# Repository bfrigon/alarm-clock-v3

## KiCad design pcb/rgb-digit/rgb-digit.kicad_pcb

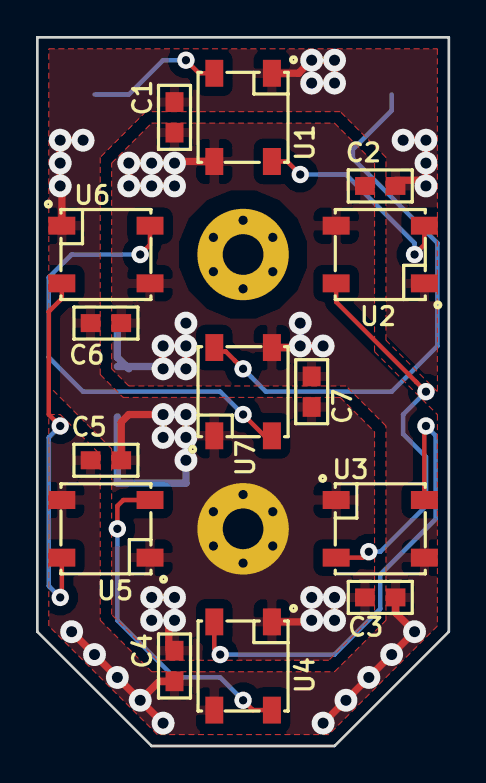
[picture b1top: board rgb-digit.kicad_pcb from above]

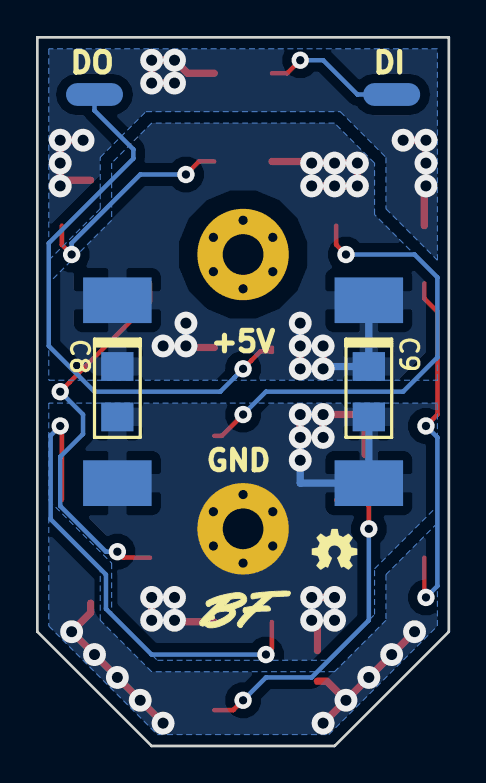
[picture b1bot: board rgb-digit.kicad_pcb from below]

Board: 2 copper layers, 22.9 x 39.4 mm, 26 parts (10 on the bottom side), 10 nets.

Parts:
C1, C2, C3, C4, C5, C6, C7: 100nF; C-0603
C8: 1uF; CPL-1206
C9: 10uF; CPL-1206
H1, H2: Hole; Hole-Screw-#2
J1: 5V IN; WP-100mil-1x01
J2: GND IN; WP-100mil-1x01
J3: 5V OUT; WP-100mil-1x01
J4: GND OUT; WP-100mil-1x01
J5: DATA IN; WP-50mil-1x01
J6: DATA OUT; WP-50mil-1x01
LOGO-OSHW-100: OSHW; LOGO-OSHW-100
SIGNATURE_SILK: LOGO; SIGNATURE_SILK
U1, U2, U3, U4, U5, U6, U7: WS2812B; LED-5050

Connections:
+5V: C1.1, C2.1, C3.1, C4.1, C5.1, C6.1, C7.1, C8.A, C9.A, J1.1, J3.1, U1.1, U2.1, U3.1, U4.1, U5.1, U6.1, U7.1
/DIN: J5.1, U1.4
/DOUT: J6.1, U7.2
GND: C1.2, C2.2, C3.2, C4.2, C5.2, C6.2, C7.2, C8.K, C9.K, H1.P, H2.P, J2.1, J4.1, U1.3, U2.3, U3.3, U4.3, U5.3, U6.3, U7.3
unnamed: U1.2, U2.4
unnamed: U2.2, U3.4
unnamed: U3.2, U4.4
unnamed: U4.2, U5.4
unnamed: U5.2, U6.4
unnamed: U6.2, U7.4

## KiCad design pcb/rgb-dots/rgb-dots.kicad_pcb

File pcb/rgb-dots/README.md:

### Bill of material ###

```
Date    : 2018-08-29
Doc. ID : CLKV3-SCH-02
Project : Alarm Clock (V3)
Title   : Display - Rgb Dots

Part #  : CLKV3-PC-02
REV.    : B

Components : 4
```

------------------------------------------------------------------------------------------------------------------------

| Qty | Ref.  | Description          | Value | Part #      | Footprint    |
|-----|-------|----------------------|-------|-------------|--------------|
| 2   | U1-U2 | Digital 5050 RGB LED | -     | IN-PI554FCH | SMT:LED-5050 |
| 2   | C1-C2 | Capacitor            | 100nF | -           | SMT-0603     |

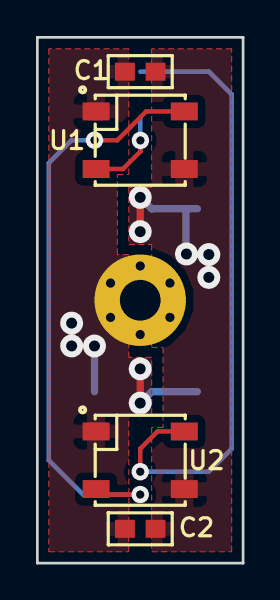
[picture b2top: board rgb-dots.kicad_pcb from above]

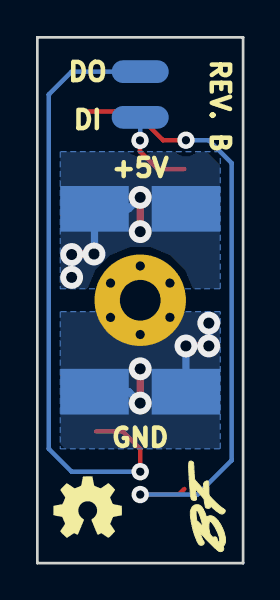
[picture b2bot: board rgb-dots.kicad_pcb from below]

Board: 2 copper layers, 11.4 x 29.2 mm, 13 parts (8 on the bottom side), 5 nets.

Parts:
C1, C2: 100nF; C-0603
H1: Hole; Hole-Screw-#2
J1: DATA IN; WP-50mil-1x01
J2: 5V IN; WP-100mil-1x01
J3: GND IN; WP-100mil-1x01
J4: 5V OUT; WP-100mil-1x01
J5: GND OUT; WP-100mil-1x01
J6: DATA OUT; WP-50mil-1x01
LOGO-OSHW-150: OSHW; LOGO-OSHW-150
SIGNATURE_SILK: LOGO; SIGNATURE_SILK
U1, U2: WS2812B; LED-5050

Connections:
+5V: C1.1, C2.1, J2.1, J4.1, U1.1, U2.1
/DIN: J1.1, U1.4
/DOUT: J6.1, U2.2
GND: C1.2, C2.2, H1.P, J3.1, J5.1, U1.3, U2.3
unnamed: U1.2, U2.4
